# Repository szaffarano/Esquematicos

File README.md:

Esquematicos
============

Esquemáticos de KiCad

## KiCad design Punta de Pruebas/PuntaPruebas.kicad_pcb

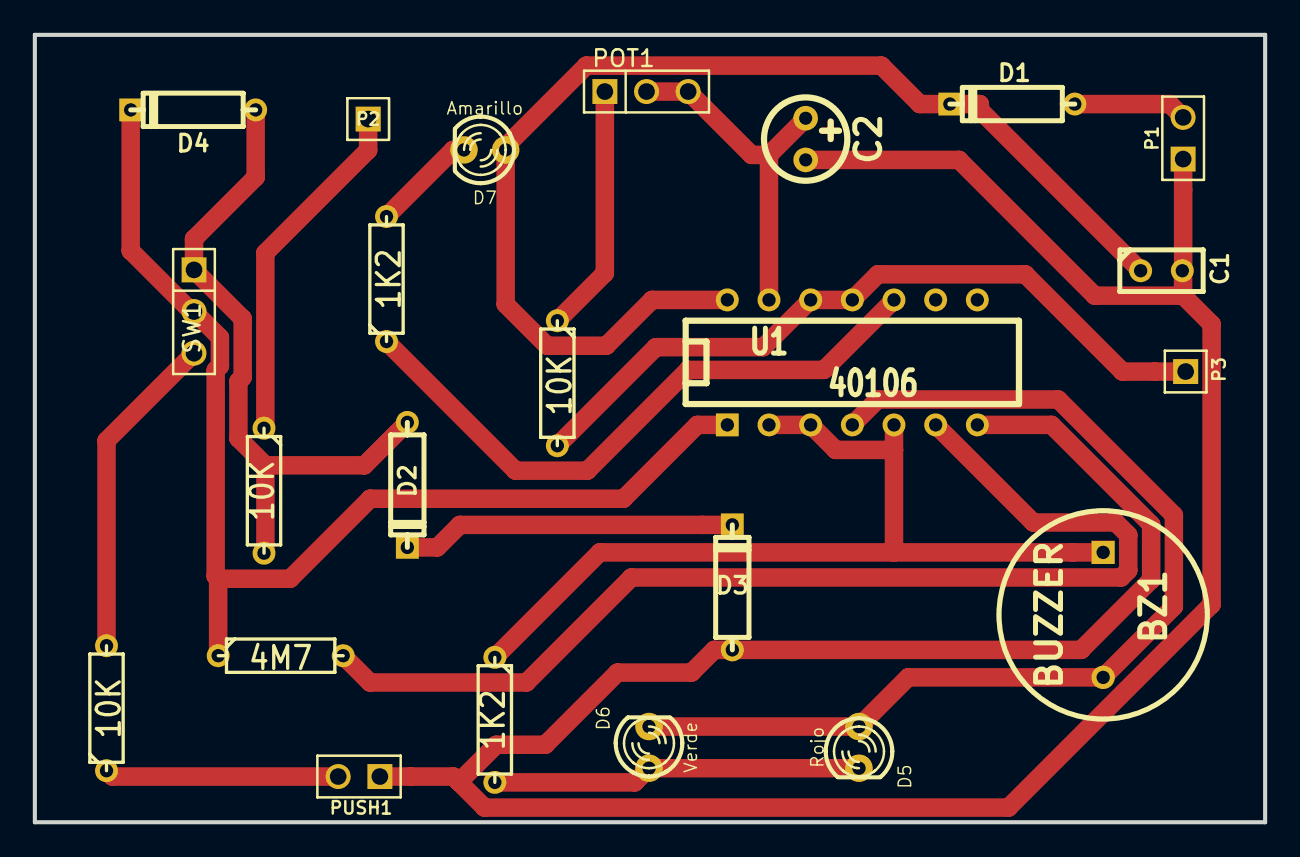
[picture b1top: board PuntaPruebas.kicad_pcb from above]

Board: 2 copper layers, 75.0 x 48.0 mm, 23 parts (0 on the bottom side), 18 nets.

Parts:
BZ1: BUZZER; BUZ3-5
C1: 0.1 uF 50V; C1
C2: 1 uF; Elko_vert_DM5_RM2-5
D1: 1N4007; D3
D2, D3: ZENER 12V; D3
D4: 4148; D3
D5: Rojo; LED-3MM
D6: Verde; LED-3MM
D7: Amarillo; LED-3MM
P1: CONN_2; PIN_ARRAY_2X1
P2, P3: CONN_1; PIN_ARRAY_1
POT1: 1M; PIN_ARRAY_3X1
PUSH1: Pulsador; PIN_ARRAY_2X1
R1, R2, R3: 10K; R3
R4: 4M7; R3
R5, R6: 1K2; R3
SW1: Llave Inversora; PIN_ARRAY_3X1
U1: 40106; DIP-14__300

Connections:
unnamed: D5.2, D6.1, R5.2
unnamed: BZ1.1, R5.1, U1.2, U1.3, U1.5
unnamed: BZ1.2, D5.1, D6.2, U1.4
unnamed: D2.2, D3.2
unnamed: D2.1, D4.1, R1.2, SW1.1
unnamed: D1.1, P1.2
unnamed: D4.2, R4.1, SW1.2, U1.1
unnamed: R4.2, U1.6
unnamed: R2.2, SW1.3
unnamed: PUSH1.2, R2.1
unnamed: P3.1, R3.2, U1.11, U1.12
unnamed: C2.1, POT1.2, POT1.3, U1.13
unnamed: POT1.1, R3.1
unnamed: R6.1, U1.10
unnamed: P2.1, R1.1
unnamed: D7.2, R6.2
VDD: C1.1, D1.2, D7.1, U1.14
VSS: C1.2, C2.2, D3.1, P1.1, PUSH1.1, U1.7

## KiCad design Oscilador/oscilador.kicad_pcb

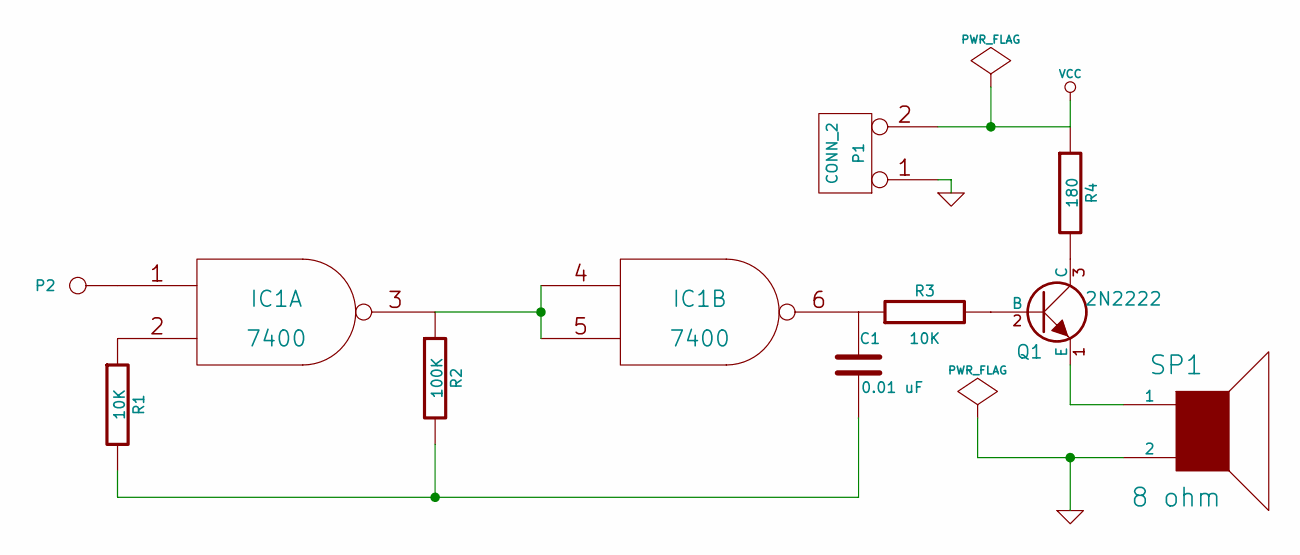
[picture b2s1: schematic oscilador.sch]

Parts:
C1: 0.01 uF
IC1: 7400
P1: CONN_2
P2: CONN_1
Q1: 2N2222
R1, R3: 10K
R2: 100K
R4: 180
SP1: 8 ohm

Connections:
GND: IC1.7 (GND), P1.1, SP1.2
unnamed: Q1.2 (B), R3.2
unnamed: Q1.3 (C), R4.2
unnamed: Q1.1 (E), SP1.1
unnamed: IC1.1, P2.1
unnamed: IC1.2, R1.1
unnamed: IC1.3, IC1.4, IC1.5, R2.1
unnamed: C1.1, IC1.6, R3.1
unnamed: C1.2, R1.2, R2.2
VCC: IC1.14 (VCC), P1.2 (PM), R4.1

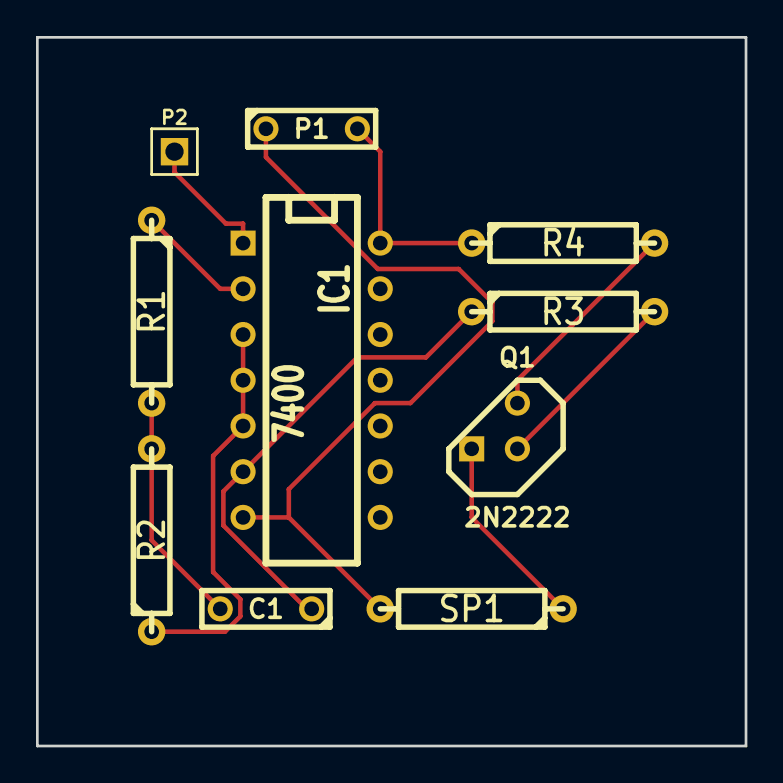
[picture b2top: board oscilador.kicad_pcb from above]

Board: 2 copper layers, 39.4 x 39.4 mm, 10 parts (0 on the bottom side), 10 nets.

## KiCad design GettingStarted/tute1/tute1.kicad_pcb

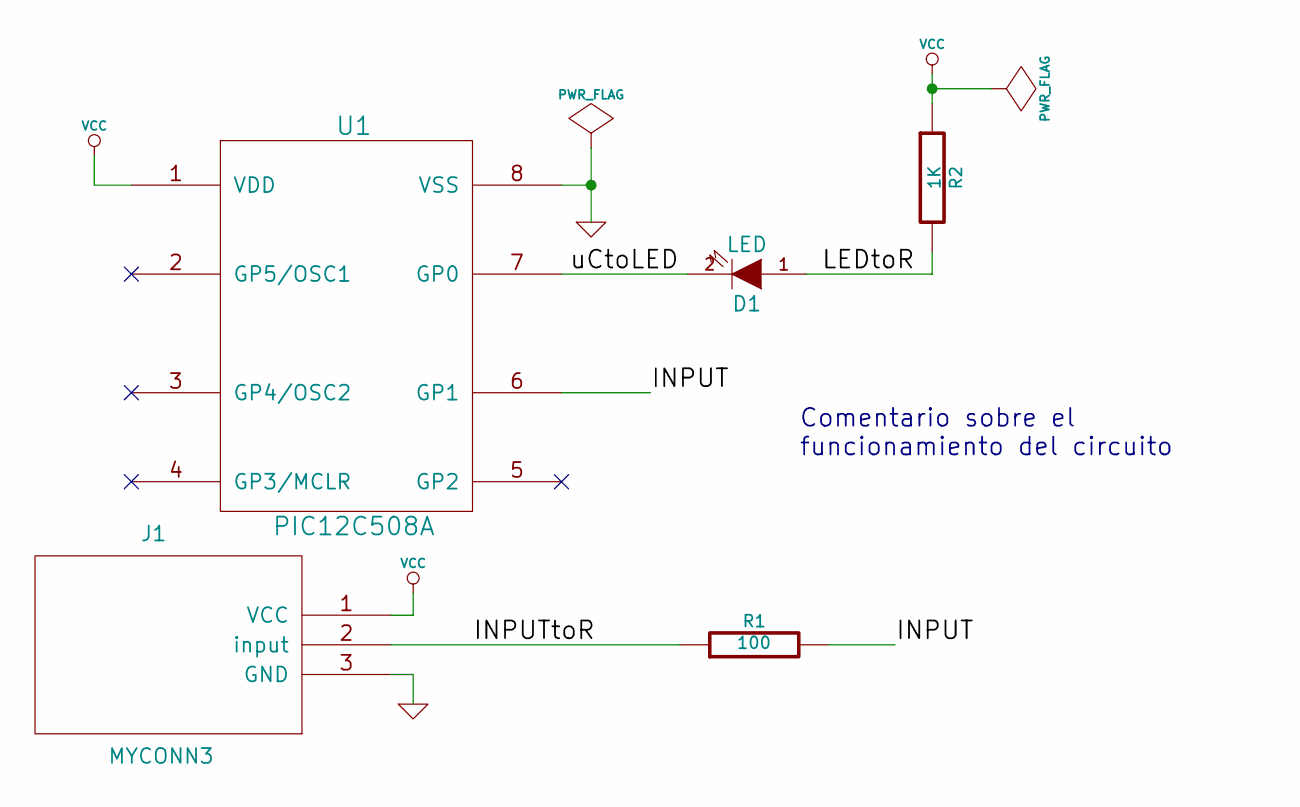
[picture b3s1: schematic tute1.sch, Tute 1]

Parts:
D1: LED
J1: MYCONN3; MODULE
R1: 100
R2: 1K
U1: PIC12C508A

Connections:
/INPUT: R1.2, U1.6 (GP1)
/INPUTtoR: J1.2 (input), R1.1
/LEDtoR: D1.1 (A), R2.2
/uCtoLED: D1.2 (K), U1.7 (GP0)
GND: J1.3 (GND), U1.8 (VSS)
VCC: J1.1 (VCC), R2.1, U1.1 (VDD)

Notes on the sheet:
Comentario sobre el funcionamiento del circuito

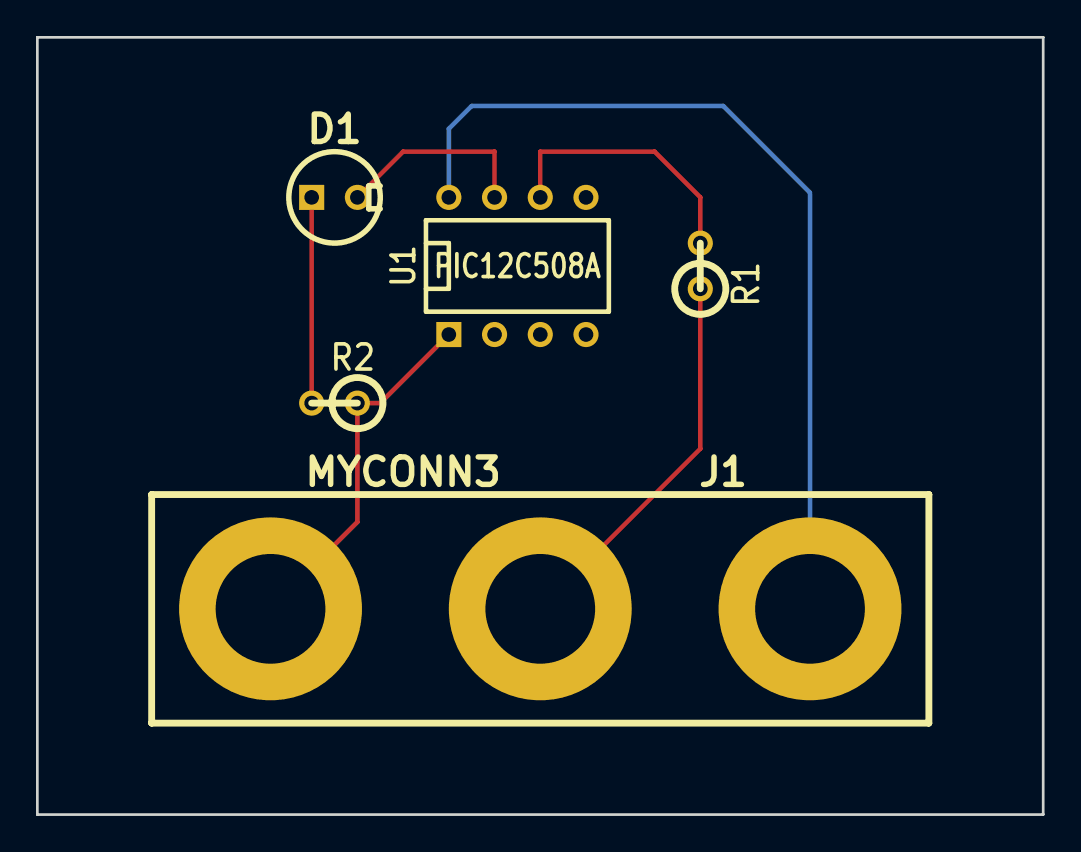
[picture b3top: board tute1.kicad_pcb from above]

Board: 2 copper layers, 55.9 x 43.2 mm, 5 parts (0 on the bottom side), 6 nets.

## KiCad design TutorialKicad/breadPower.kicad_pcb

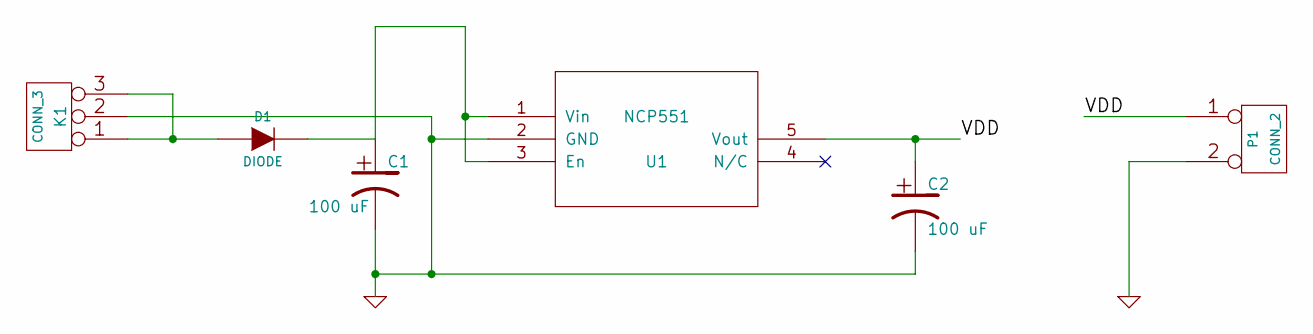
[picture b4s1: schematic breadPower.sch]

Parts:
C1, C2: 100 uF
D1: DIODE
K1: CONN_3
P1: CONN_2
U1: NCP551; MODULE

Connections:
/VDD: C2.1, P1.1, U1.5 (Vout)
GND: C1.2, C2.2, K1.2 (PM), P1.2 (PM), U1.2 (GND)
unnamed: D1.1 (A), K1.1, K1.3
unnamed: C1.1, D1.2 (K), U1.1 (Vin), U1.3 (En)

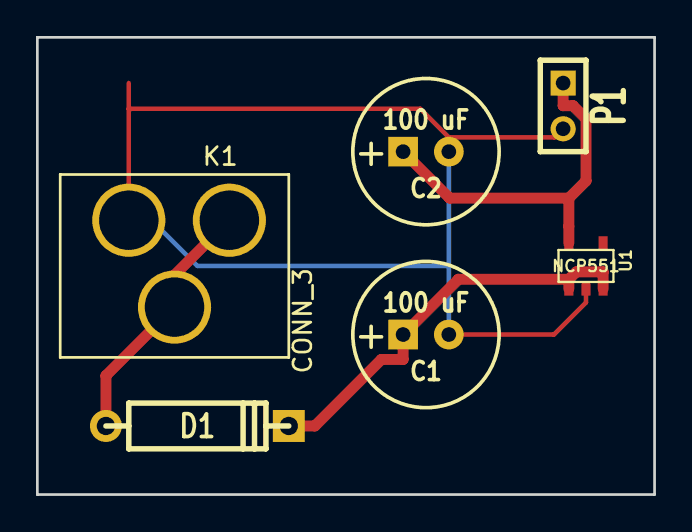
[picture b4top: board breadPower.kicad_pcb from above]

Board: 2 copper layers, 34.3 x 25.4 mm, 6 parts (0 on the bottom side), 4 nets.

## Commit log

2013-10-30 Inicio proyecto con esquemáticos de kicad
2013-11-05 Siguiendo ejemplos de otro tutorial
2013-11-06 Avances con la punta de pruebas
2013-11-06 Pruebas con compuertas y pines ocultos en componentes dil
2013-11-06 mejora en el diseño del esquema y del pcb, agregado de modulos y librerias kicad para uso en todos los proyectos
2013-11-06 Realizo un layout alternativo del PCB, haciendo más claro el ensamblado
2013-11-07 cambio de layout nuevamente, agrando el ancho de las vías para facilitar impresión
2013-11-07 generacion de esquema en pdf
2013-11-09 PCB definitivo, incremento ancho de pista y mejoras en los archivos gerber
2013-11-27 Agrando pistas e impreso para mayor comodidad y adaptarlo al gabinete a usar
